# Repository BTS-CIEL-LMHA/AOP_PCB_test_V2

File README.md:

Ce PCB a été crée pour expérimenter sur différents montages d'amplificateurs opérationnels.

Le principe est d'utiliser 2 cavaliers pour sélectionner le montage utilisé : un pour l'entrée, l'autre pour la sortie.

2 cavaliers à l'entrée et à la sortie du PCB permettent de court-circuiter les condensateurs de liaison pour obtenir une entrée avec offset (indispensable cf ci-dessous)

ATTENTION : il ne faut pas avoir plusieurs cavaliers sur des sorties au risque de court circuit et de destruction des AOP

(on peut avoir plusieurs cavaliers sur les entrées mais c'est déconseillé et cela peut créer des effets indésirables : injection de tension d'un montage à l'autre)

REMARQUE : Les amplis inverseurs et les filtres passe-haut et passe-bande ne sont pas utilisables car l'entrée + est reliée directement ou par une résistance à la masse (au lieu du point milieu de l'alimentation = masse virtuelle)

Les amplis non inverseurs sont utilisable à condition d'avoir un offset (1/2 alimentation) sur le signal d'entrée.

Il est possible assez facilement de modifier les filtres passe-haut et passe-bande en remplaçant la résistance qui va vers la masse par une résistance qui va vers une masse virtuelle.

Pour les amplis inverseur la connexion à la masse étant directe la modification est plus complexe (couper la connexion à la masse du PCB et installer un fil vers la masse virtuelle).

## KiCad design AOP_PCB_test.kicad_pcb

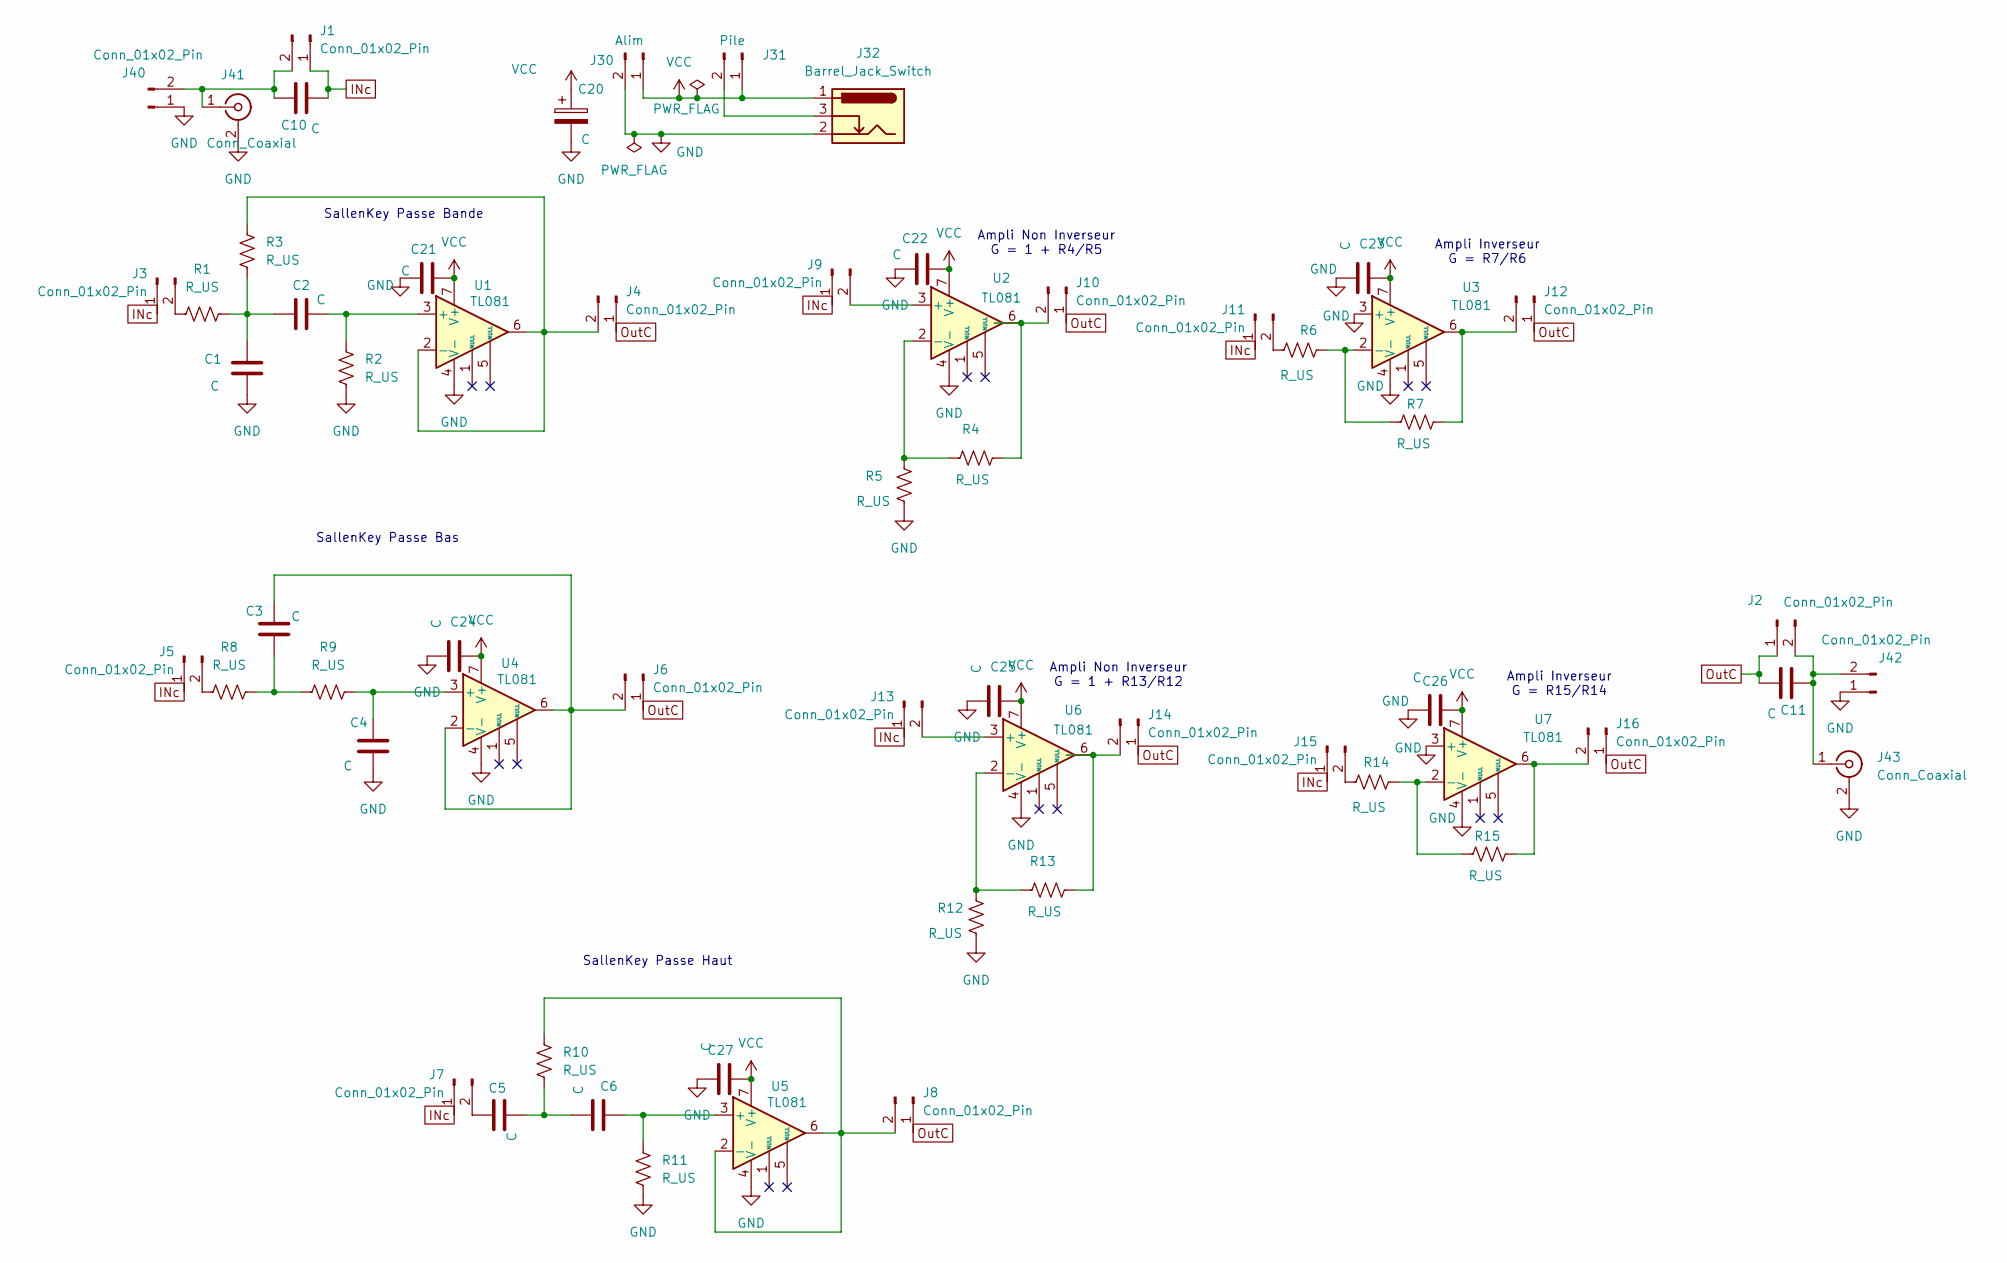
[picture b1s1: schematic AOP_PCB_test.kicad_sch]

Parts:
C1, C2, C3, C4, C5, C6, C10, C11, C21, C22, C23, C24, C27: C; C_Rect_L11.5mm_W3.6mm_P10.00mm_MKT
C20: C; C_Radial_D10.0mm_H12.5mm_P5.00mm
C25, C26: C; C_1206_3216Metric_Pad1.33x1.80mm_HandSolder
J1, J2, J3, J4, J5, J6, J7, J8, J9, J10, J11, J12, J13, J14, J15, J16, J40, J42: Conn_01x02_Pin; PinHeader_1x02_P2.54mm_Vertical
J30: Alim; PinHeader_1x02_P2.54mm_Vertical
J31: Pile; PinHeader_1x02_P2.54mm_Vertical
J32: Barrel_Jack_Switch; BarrelJack_Wuerth_6941xx301002
J41, J43: Conn_Coaxial; BNC_Amphenol_B6252HB-NPP3G-50_Horizontal
R1, R2, R3, R4, R5, R6, R7, R8, R9, R10, R11: R_US; R_Axial_DIN0204_L3.6mm_D1.6mm_P7.62mm_Horizontal
R12, R13, R14, R15: R_US; R_1206_3216Metric_Pad1.30x1.75mm_HandSolder
U1, U2, U3, U4, U5: TL081; DIP-8_W7.62mm_Socket_LongPads
U6, U7: TL081; SOIC-8_3.9x4.9mm_P1.27mm

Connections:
GND: C1.2, C4.2, C20.2, C21.2, C22.2, C23.2, C24.2, C25.2, C26.2, C27.2, J30.2, J32.2, J40.1, J41.2 (Ext), J42.1, J43.2 (Ext), R2.1, R5.1, R11.2, R12.1, U1.4 (V-), U2.4 (V-), U3.3 (+), U3.4 (V-), U4.4 (V-), U5.4 (V-), U6.4 (V-), U7.3 (+), U7.4 (V-)
INc: C10.1, J1.1, J3.1, J5.1, J7.1, J9.1, J11.1, J13.1, J15.1
unnamed: C1.1, C2.2, R1.1, R3.2
unnamed: C3.2, R8.1, R9.2
unnamed: C5.1, C6.2, R10.1
unnamed: C10.2, J1.2, J40.2, J41.1 (In)
unnamed: C11.2, J2.2, J42.2, J43.1 (In)
unnamed: J3.2, R1.2
unnamed: J4.2, R3.1, U1.2 (-), U1.6
unnamed: J5.2, R8.2
unnamed: C3.1, J6.2, U4.2 (-), U4.6
unnamed: C5.2, J7.2
unnamed: J8.2, R10.2, U5.2 (-), U5.6
unnamed: J9.2, U2.3 (+)
unnamed: J10.2, R4.2, U2.6
unnamed: J11.2, R6.2
unnamed: J12.2, R7.2, U3.6
unnamed: J13.2, U6.3 (+)
unnamed: J14.2, R13.2, U6.6
unnamed: J15.2, R14.2
unnamed: J16.2, R15.2, U7.6
unnamed: J31.2, J32.3
unnamed: C2.1, R2.2, U1.3 (+)
unnamed: R4.1, R5.2, U2.2 (-)
unnamed: R6.1, R7.1, U3.2 (-)
unnamed: C4.1, R9.1, U4.3 (+)
unnamed: C6.1, R11.1, U5.3 (+)
unnamed: R12.2, R13.1, U6.2 (-)
unnamed: R14.1, R15.1, U7.2 (-)
OutC: C11.1, J2.1, J4.1, J6.1, J8.1, J10.1, J12.1, J14.1, J16.1
VCC: C20.1, C21.1, C22.1, C23.1, C24.1, C25.1, C26.1, C27.1, J30.1, J31.1, J32.1, U1.7 (V+), U2.7 (V+), U3.7 (V+), U4.7 (V+), U5.7 (V+), U6.7 (V+), U7.7 (V+)

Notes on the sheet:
Ampli Non Inverseur G = 1 + R4/R5
SallenKey Passe Bas
Ampli Non Inverseur G = 1 + R13/R12
Ampli Inverseur G = R15/R14
SallenKey Passe Haut
Ampli Inverseur G = R7/R6
SallenKey Passe Bande

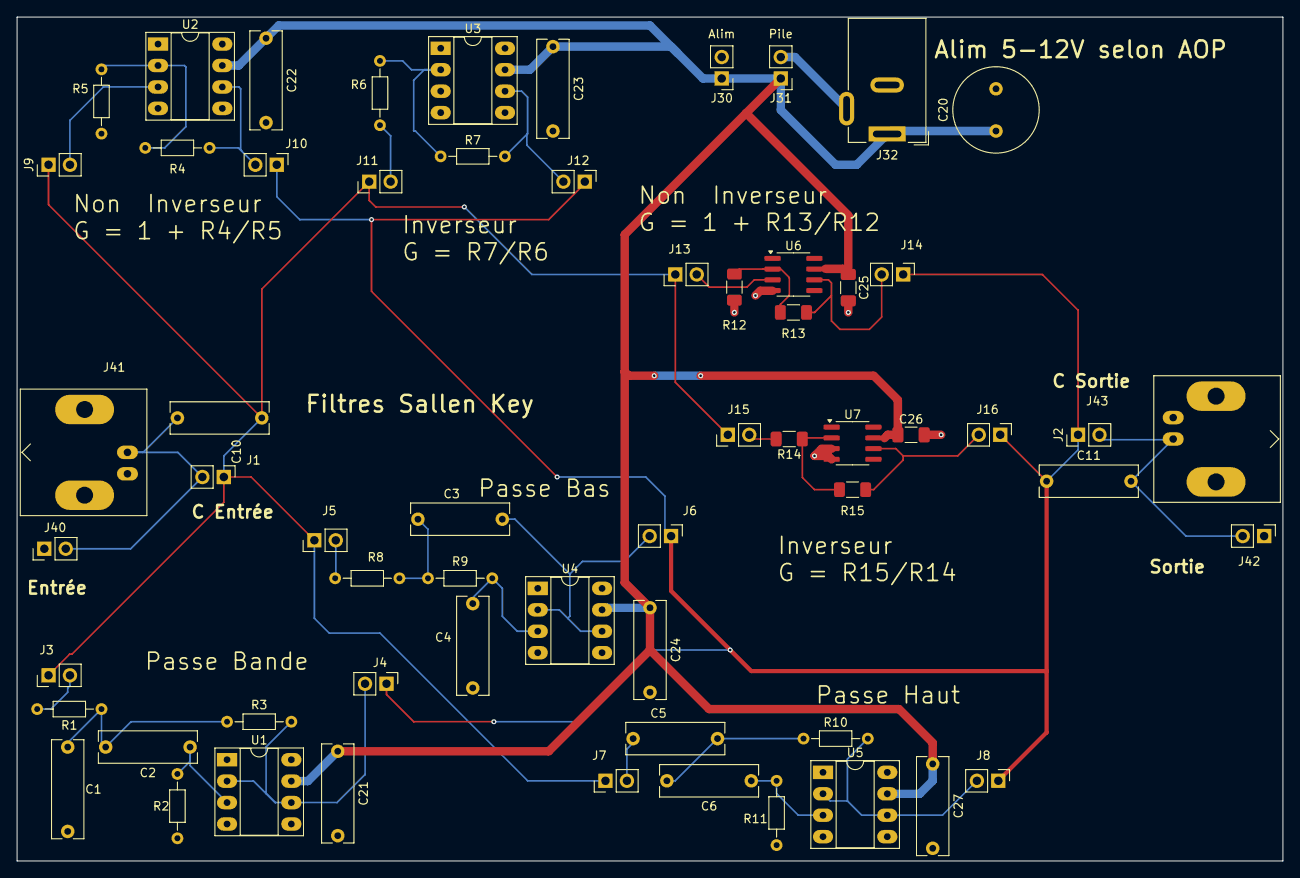
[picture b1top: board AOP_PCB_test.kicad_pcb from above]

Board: 2 copper layers, 150.0 x 100.0 mm, 61 parts (0 on the bottom side), 31 nets.

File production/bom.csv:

Designator,Footprint,Quantity,Value,LCSC Part #
"C1, C10, C11, C2, C21, C22, C23, C24, C27, C3, C4, C5, C6",C_Rect_L11.5mm_W3.6mm_P10.00mm_MKT,13,C,
C20,C_Radial_D10.0mm_H12.5mm_P5.00mm,1,C,
"C25, C26",1206,2,C,
"J1, J10, J11, J12, J13, J14, J15, J16, J2, J3, J4, J40, J42, J5, J6, J7, J8, J9",PinHeader_1x02_P2.54mm_Vertical,18,Conn_01x02_Pin,
J30,PinHeader_1x02_P2.54mm_Vertical,1,Alim,
J31,PinHeader_1x02_P2.54mm_Vertical,1,Pile,
J32,BarrelJack_Wuerth_6941xx301002,1,Barrel_Jack_Switch,
"J41, J43",BNC_Amphenol_B6252HB-NPP3G-50_Horizontal,2,Conn_Coaxial,
"R1, R10, R11, R2, R3, R4, R5, R6, R7, R8, R9",R_Axial_DIN0204_L3.6mm_D1.6mm_P7.62mm_Horizontal,11,R_US,
"R12, R13, R14, R15",1206,4,R_US,
"U1, U2, U3, U4, U5",DIP-8_W7.62mm_Socket_LongPads,5,TL081,
"U6, U7",SOIC-8_3.9x4.9mm_P1.27mm,2,TL081,
